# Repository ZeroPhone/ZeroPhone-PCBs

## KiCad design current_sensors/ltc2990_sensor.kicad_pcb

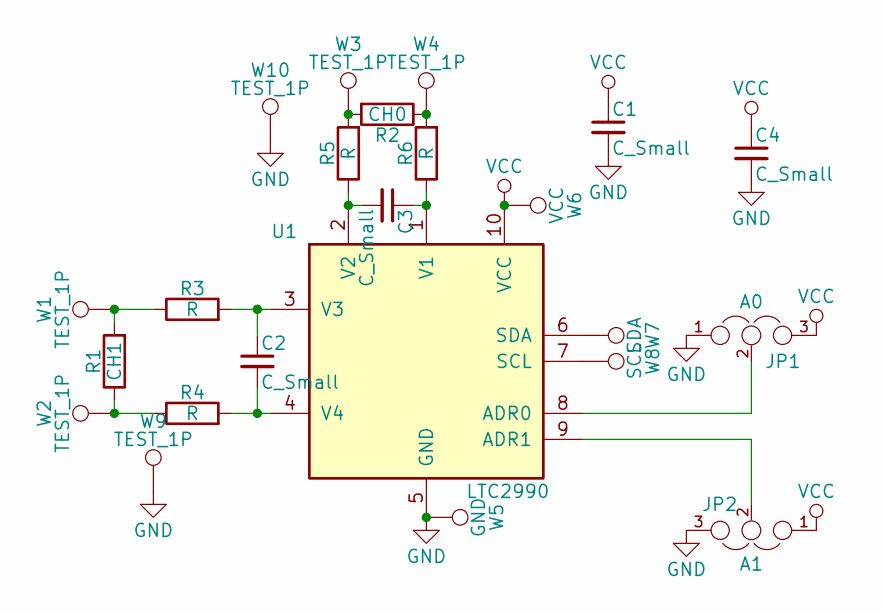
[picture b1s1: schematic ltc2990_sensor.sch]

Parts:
C1, C2, C3, C4: C_Small; R_0603
JP1: A0; GS3_SMALL
JP2: A1; GS3_SMALL
R1: CH1; R_2512_HandSoldering
R2: CH0; R_2512_HandSoldering
R3, R4, R5, R6: R; R_0603
U1: LTC2990; MSOP-10_3x3mm_Pitch0.5mm
W1, W2, W3, W4, W9, W10: TEST_1P; Measurement_Point_Square-SMD-Pad_Big
W5: GND; Measurement_Point_Square-SMD-Pad_Small
W6: VCC; Measurement_Point_Square-SMD-Pad_Small
W7: SDA; Measurement_Point_Square-SMD-Pad_Small
W8: SCL; Measurement_Point_Square-SMD-Pad_Small

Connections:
GND: C1.2, C4.2, JP1.1, JP2.3, U1.5 (GND), W5.1, W9.1, W10.1
unnamed: C2.1, R3.2, U1.3 (V3)
unnamed: C2.2, R4.2, U1.4 (V4)
unnamed: C3.1, R6.1, U1.1 (V1)
unnamed: C3.2, R5.1, U1.2 (V2)
unnamed: JP1.2, U1.8 (ADR0)
unnamed: JP2.2, U1.9 (ADR1)
unnamed: R1.1, R4.1, W2.1
unnamed: R1.2, R3.1, W1.1
unnamed: R2.1, R6.2, W4.1
unnamed: R2.2, R5.2, W3.1
unnamed: U1.6 (SDA), W7.1
unnamed: U1.7 (SCL), W8.1
VCC: C1.1, C4.1, JP1.3, JP2.1, U1.10 (VCC), W6.1

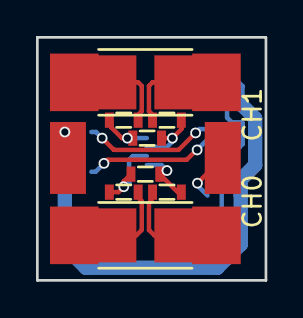
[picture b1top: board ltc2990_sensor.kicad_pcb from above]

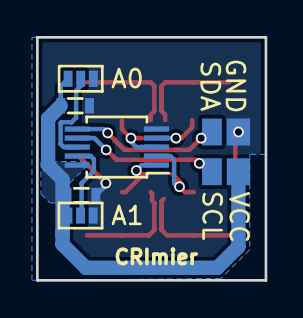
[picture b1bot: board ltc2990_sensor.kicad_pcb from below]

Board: 2 copper layers, 12.7 x 13.5 mm, 23 parts (9 on the bottom side), 14 nets.

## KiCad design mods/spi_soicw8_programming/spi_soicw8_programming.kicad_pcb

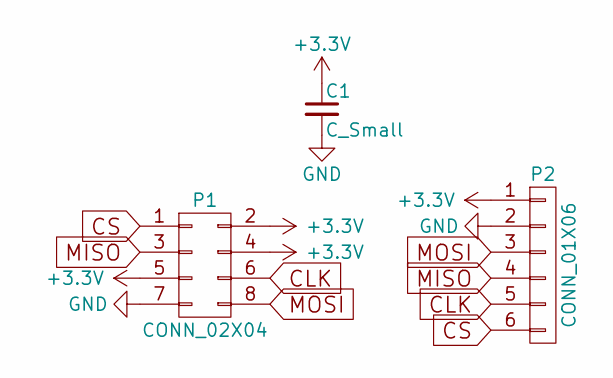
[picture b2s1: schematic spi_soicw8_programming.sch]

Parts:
C1: C_Small; C_0805_HandSoldering
P1: CONN_02X04; SOIJ-8_5.3x5.3mm_Pitch1.27mm
P2: CONN_01X06; Pin_Header_Straight_1x06_Pitch2.54mm

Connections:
+3V3: C1.1, P1.2, P1.4, P1.5, P2.1
CLK: P1.6, P2.5
CS: P1.1, P2.6
GND: C1.2, P1.7, P2.2
MISO: P1.3, P2.4
MOSI: P1.8, P2.3

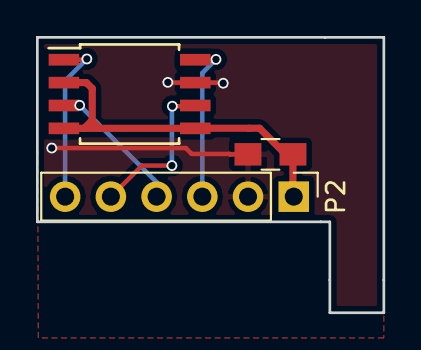
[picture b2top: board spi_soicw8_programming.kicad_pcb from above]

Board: 2 copper layers, 19.2 x 15.3 mm, 3 parts (0 on the bottom side), 6 nets.

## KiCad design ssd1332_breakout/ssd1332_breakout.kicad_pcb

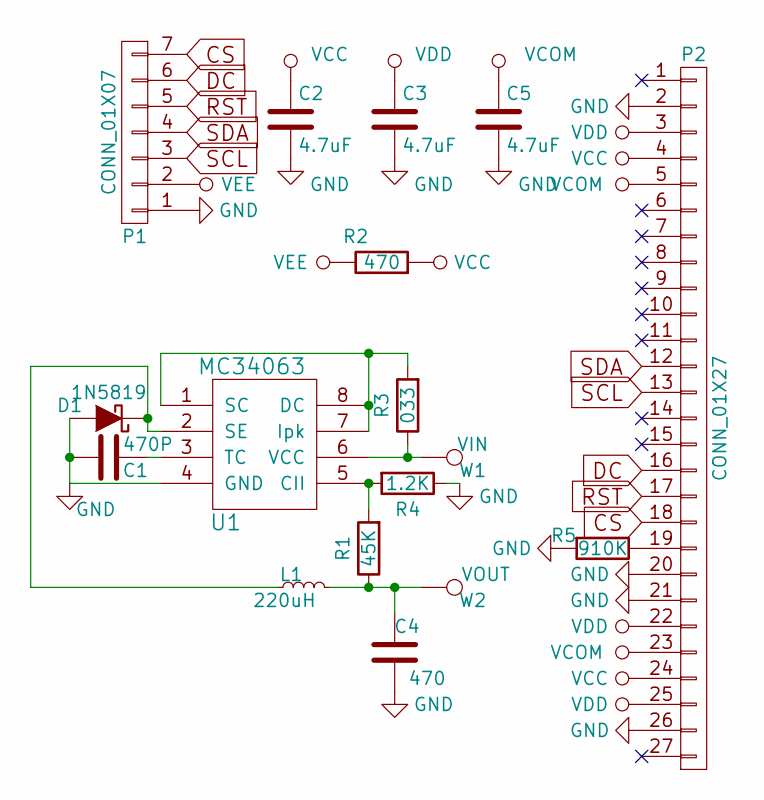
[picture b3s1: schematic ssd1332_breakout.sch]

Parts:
C1: 470P; C_0805_HandSoldering
C2, C3, C5: 4.7uF; C_0805_HandSoldering
C4: 470; C_0805_HandSoldering
D1: 1N5819; D_MiniMELF_Handsoldering
L1: 220uH; Choke_SMD_1206_Handsoldering
P1: CONN_01X07; Pin_Header_Straight_1x07_Pitch2.54mm
P2: CONN_01X27; FPC_27
R1: 45K; R_0805_HandSoldering
R2: 470; R_0805_HandSoldering
R3: 033; R_0805_HandSoldering
R4: 1.2K; R_0805_HandSoldering
R5: 910K; R_0805_HandSoldering
U1: MC34063; SOIC-8_3.9x4.9mm_Pitch1.27mm
W1: VIN; Measurement_Point_Square-SMD-Pad_Small
W2: VOUT; Measurement_Point_Square-SMD-Pad_Small

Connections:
CS: P1.7, P2.18
DC: P1.6, P2.16
GND: C1.2, C2.2, C3.2, C4.1, C5.2, D1.2 (A), P1.1, P2.2, P2.20, P2.21, P2.26, R4.1, R5.2, U1.4 (GND)
unnamed: C1.1, U1.3 (TC)
unnamed: C4.2, L1.2, R1.1, W2.1
unnamed: D1.1 (K), L1.1, U1.2 (SE)
unnamed: P2.19, R5.1
unnamed: R1.2, R4.2, U1.5 (CII)
unnamed: R3.1, U1.6 (VCC), W1.1
unnamed: R3.2, U1.1 (SC), U1.7 (Ipk), U1.8 (DC)
RST: P1.5, P2.17
SCL: P1.3, P2.13
SDA: P1.4, P2.12
VCC: C2.1, P2.4, P2.24, R2.2
VCOM: C5.1, P2.5, P2.23
VDD: C3.1, P2.3, P2.22, P2.25
VEE: P1.2, R2.1

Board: 2 copper layers, 17 parts (16 on the bottom side), 17 nets, no tracks yet.

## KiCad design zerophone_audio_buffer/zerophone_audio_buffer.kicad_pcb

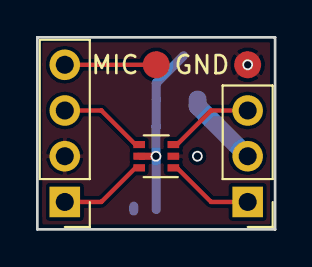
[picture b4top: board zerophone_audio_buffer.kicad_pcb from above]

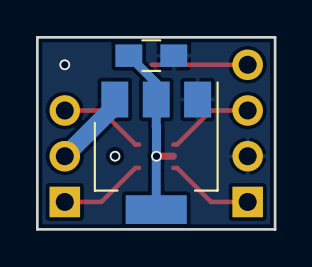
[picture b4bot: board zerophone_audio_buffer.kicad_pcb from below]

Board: 2 copper layers, 13.2 x 10.7 mm, 7 parts (2 on the bottom side), 8 nets.

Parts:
C1: C_Small; C_0805_HandSoldering
P1: INPUT_CONN; Pin_Header_Straight_1x03_Pitch2.54mm
P2: OUTPUT_CONN; Pin_Header_Straight_1x04_Pitch2.54mm
U1: LM1117-2.5; SOT-223
U2: NC7WZ16; SOT-363_SC-70-6
W1: MIC; Measurement_Point_Round-SMD-Pad_Small
W2: GND; Measurement_Point_Round-SMD-Pad_Small

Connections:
+2V5: C1.1, U1.2, U1.4, U2.5
+3V3: P1.2, U1.3
GND: C1.2, P2.2, U1.1, U2.2, W2.1
unnamed: P1.1, U2.1
unnamed: P1.3, U2.3
unnamed: P2.1, U2.6
unnamed: P2.3, U2.4
unnamed: P2.4, W1.1
